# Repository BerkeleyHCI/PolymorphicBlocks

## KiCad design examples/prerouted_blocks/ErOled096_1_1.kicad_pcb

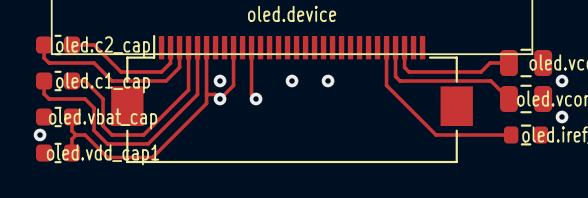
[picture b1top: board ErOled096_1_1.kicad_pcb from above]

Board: 4 copper layers, 9 parts (0 on the bottom side), 10 nets.

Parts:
oled.c1_cap, oled.c2_cap, oled.vbat_cap, oled.vdd_cap1: C_0603_1608Metric
oled.device: AFC01-S30FCA-00; Hirose_FH12-30S-0.5SH_1x30-1MP_P0.50mm_Horizontal
oled.iref_res: R_0603_1608Metric
oled.lcd: ER-OLED-0.96-1.1; Lcd_Er_Oled0.96_1.1_Outline
oled.vcc_cap, oled.vcomh_cap: C_0805_2012Metric

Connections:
gnd: oled.device.1, oled.device.8, oled.device.10, oled.device.12, oled.device.13, oled.device.15, oled.device.16, oled.device.17, oled.device.21, oled.device.22, oled.device.23, oled.device.24, oled.device.25, oled.device.29, oled.device.30, oled.iref_res.2, oled.vbat_cap.2, oled.vcc_cap.2, oled.vcomh_cap.2, oled.vdd_cap1.2
i2c_pull.i2c.sda: oled.device.19, oled.device.20
oled.c1_cap.neg: oled.c1_cap.2, oled.device.5
oled.c1_cap.pos: oled.c1_cap.1, oled.device.4
oled.c2_cap.neg: oled.c2_cap.2, oled.device.3
oled.c2_cap.pos: oled.c2_cap.1, oled.device.2
oled.device.vcc: oled.device.28, oled.vcc_cap.1
oled.device.vcomh: oled.device.27, oled.vcomh_cap.1
oled.iref_res.a: oled.device.26, oled.iref_res.1
v3v3: oled.device.6, oled.device.9, oled.device.11, oled.vbat_cap.1, oled.vdd_cap1.1

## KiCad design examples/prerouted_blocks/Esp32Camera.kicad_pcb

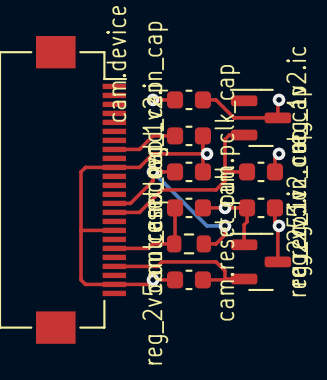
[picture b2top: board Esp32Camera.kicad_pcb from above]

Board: 2 copper layers, 11 parts (0 on the bottom side), 7 nets.

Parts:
cam.device: AFC01-S24FCA-00 (Jushuo); Hirose_FH12-24S-0.5SH_1x24-1MP_P0.50mm_Horizontal
cam.dovdd_cap, cam.pclk_cap, cam.reset_cap: C_0603_1608Metric
cam.reset_pull: R_0603_1608Metric
reg_1v2.ic: XC6206P122MR-G (Torex Semiconductor Ltd); SOT-23
reg_1v2.in_cap, reg_1v2.out_cap, reg_2v5.in_cap, reg_2v5.out_cap: C_0603_1608Metric
reg_2v5.ic: XC6206P252MR (Torex Semiconductor Ltd); SOT-23

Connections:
cam.device.reset: cam.device.19, cam.reset_cap.1, cam.reset_pull.2
cam.dvp8.pclk: cam.device.8, cam.pclk_cap.1
gnd: cam.device.10, cam.device.17, cam.device.23, cam.dovdd_cap.2, cam.pclk_cap.2, cam.reset_cap.2, reg_1v2.ic.1, reg_1v2.in_cap.2, reg_1v2.out_cap.2, reg_2v5.ic.1, reg_2v5.in_cap.2, reg_2v5.out_cap.2
pwr: reg_1v2.ic.3, reg_1v2.in_cap.1, reg_2v5.ic.3, reg_2v5.in_cap.1
v1v2: cam.device.15, reg_1v2.ic.2, reg_1v2.out_cap.1
v2v5: cam.device.21, reg_2v5.ic.2, reg_2v5.out_cap.1
v3v3: cam.device.14, cam.dovdd_cap.1, cam.reset_pull.1

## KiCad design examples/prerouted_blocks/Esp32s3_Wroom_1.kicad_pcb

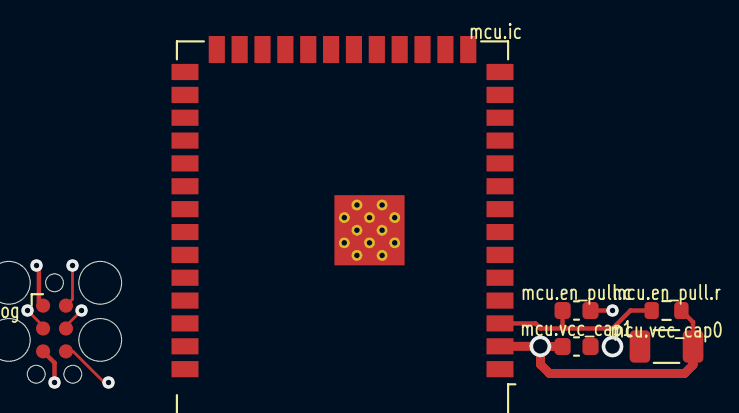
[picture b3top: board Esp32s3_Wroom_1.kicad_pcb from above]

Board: 4 copper layers, 6 parts (0 on the bottom side), 6 nets.

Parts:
mcu.en_pull.c, mcu.vcc_cap1: C_0603_1608Metric
mcu.en_pull.r: R_0603_1608Metric
mcu.ic: ESP32-S3-WROOM-1-N16R8; ESP32-S3-WROOM-1
mcu.prog: Tag-Connect_TC2030-IDC-FP_2x03_P1.27mm_Vertical
mcu.vcc_cap0: C_1206_3216Metric

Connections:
gnd: mcu.en_pull.c.2, mcu.ic.1, mcu.ic.40, mcu.ic.41, mcu.prog.5, mcu.vcc_cap0.2, mcu.vcc_cap1.2
mcu.program_boot_node: mcu.ic.27, mcu.prog.2
mcu.program_en_node: mcu.en_pull.c.1, mcu.en_pull.r.2, mcu.ic.3, mcu.prog.6
mcu.program_uart_node.a_tx: mcu.ic.37, mcu.prog.3
mcu.program_uart_node.b_tx: mcu.ic.36, mcu.prog.4
v3v3: mcu.en_pull.r.1, mcu.ic.2, mcu.prog.1, mcu.vcc_cap0.1, mcu.vcc_cap1.1

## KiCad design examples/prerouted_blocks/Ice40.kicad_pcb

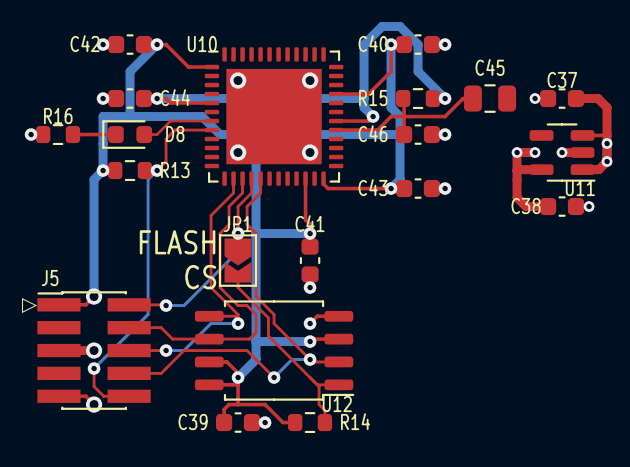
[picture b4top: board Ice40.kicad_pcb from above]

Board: 2 copper layers, 20 parts (0 on the bottom side), 12 nets.

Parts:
C37, C38, C39, C40, C41, C42, C43, C44, C46: C_0603_1608Metric
C45: C_0805_2012Metric
D8: KT-0603R (Hubei KENTO Elec) - Red 615~630nm 1.9~2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; LED_0603_1608Metric
J5: PinHeader1.27 Shrouded 2x5 (Generic); PinHeader_2x05_P1.27mm_Vertical_SMD
JP1: SolderJumper-2_P1.3mm_Open_TrianglePad1.0x1.5mm
R13, R14, R15, R16: R_0603_1608Metric
U10: ICE40UP5K-SG48 (Lattice Semiconductor Corporation); QFN-48-1EP_7x7mm_P0.5mm_EP5.3x5.3mm
U11: LP5907MFX-1.2/NOPB (Texas Instruments); SOT-23-5
U12: W25Q128JVSIQ (Winbond Electronics); SOIC-8_5.23x5.23mm_P1.27mm

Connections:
cdone.res.a: D8.1, R16.1
fpga.cdone: D8.2, U10.7
fpga.cs_jmp.output: JP1.2, R14.2, U12.1
fpga.ic.creset_b: J5.10, R13.2, U10.8
fpga.ic.spi_config.miso: J5.8, U10.17, U12.2
fpga.ic.spi_config.mosi: J5.6, U10.14, U12.5
fpga.ic.spi_config.sck: J5.4, U10.15, U12.6
fpga.ic.spi_config_cs: J5.2, JP1.1, U10.16
fpga.pll_res.pwr_out: C45.1, C46.1, R15.2, U10.29
fpga.vcc_reg.pwr_out: C38.1, C44.1, R15.1, U10.5, U10.30, U11.5
gnd: C37.2, C38.2, C39.2, C40.2, C41.2, C42.2, C43.2, C44.2, C45.2, C46.2, J5.3, J5.5, J5.9, R16.2, U10.49, U11.2, U12.4
v3v3: C37.1, C39.1, C40.1, C41.1, C42.1, C43.1, J5.1, R13.1, R14.1, U10.1, U10.22, U10.24, U10.33, U11.1, U11.3, U12.3, U12.7, U12.8

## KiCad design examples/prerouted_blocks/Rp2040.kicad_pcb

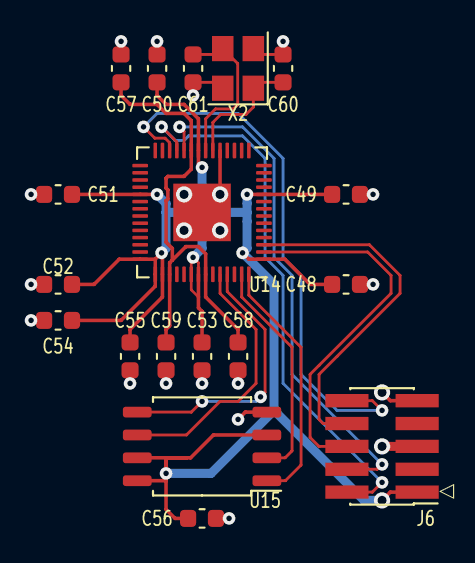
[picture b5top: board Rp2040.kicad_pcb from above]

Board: 2 copper layers, 18 parts (0 on the bottom side), 14 nets.

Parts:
C48, C49, C50, C51, C52, C53, C54, C55, C56, C57, C58, C59, C60, C61: C_0603_1608Metric
J6: PinHeader1.27 Shrouded 2x5 (Generic); PinHeader_2x05_P1.27mm_Vertical_SMD
U14: RP2040 (Raspberry Pi); QFN-56-1EP_7x7mm_P0.4mm_EP3.2x3.2mm
U15: W25Q128JVSIQ (Winbond Electronics); SOIC-8_5.23x5.23mm_P1.27mm
X2: Crystal_SMD_3225-4Pin_3.2x2.5mm

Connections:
gnd: C48.2, C49.2, C50.2, C51.2, C52.2, C53.2, C54.2, C55.2, C56.2, C57.2, C58.2, C59.2, C60.2, C61.2, J6.3, J6.5, J6.9, U14.19, U14.57, U15.4, X2.2, X2.4
mcu.crystal.crystal.a: C60.1, U14.20, X2.1
mcu.crystal.crystal.b: C61.1, U14.21, X2.3
mcu.ic.qspi.miso: U14.55, U15.2
mcu.ic.qspi.mosi: U14.53, U15.5
mcu.ic.qspi.sck: U14.52, U15.6
mcu.ic.qspi_cs: U14.56, U15.1
mcu.ic.vreg_vout: C57.1, C58.1, C59.1, U14.23, U14.45, U14.50
mcu.swd.swd.reset: J6.10, U14.26
mcu.swd.swd.swclk: J6.4, U14.24
mcu.swd.swd.swdio: J6.2, U14.25
mcu.swd.swo: J6.6, U14.2
mcu.swd.tdi: J6.8, U14.3
v3v3: C48.1, C49.1, C50.1, C51.1, C52.1, C53.1, C54.1, C55.1, C56.1, J6.1, U14.1, U14.10, U14.22, U14.33, U14.42, U14.43, U14.44, U14.48, U14.49, U15.3, U15.7, U15.8

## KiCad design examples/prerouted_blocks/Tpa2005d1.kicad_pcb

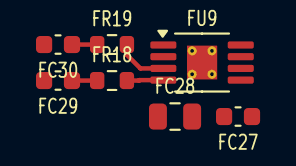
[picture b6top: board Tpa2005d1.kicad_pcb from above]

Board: 2 copper layers, 7 parts (0 on the bottom side), 6 nets.

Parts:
FC27: spk_drv.pwr_cap; C_0603_1608Metric
FC28: spk_drv.bulk_cap; C_0805_2012Metric
FC29: spk_drv.inp_cap; C_0603_1608Metric
FC30: spk_drv.inn_cap; C_0603_1608Metric
FR18: spk_drv.inp_res; R_0603_1608Metric
FR19: spk_drv.inn_res; R_0603_1608Metric
FU9: spk_drv.ic; MSOP-8-1EP_3x3mm_P0.65mm_EP1.68x1.88mm_ThermalVias

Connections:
Fgnd: FC27.2, FC28.2, FC30.2, FU9.7, FU9.9
Fspk_drv.ic.inn: FR19.2, FU9.3
Fspk_drv.ic.inp: FR18.2, FU9.4
Fspk_drv.inn_res.input: FC30.1, FR19.1
Fspk_drv.inp_res.input: FC29.1, FR18.1
Fv5: FC27.1, FC28.1, FU9.1, FU9.6

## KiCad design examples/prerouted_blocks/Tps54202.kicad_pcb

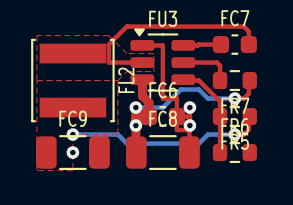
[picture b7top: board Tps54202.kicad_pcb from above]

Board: 2 copper layers, 9 parts (0 on the bottom side), 7 nets.

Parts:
FC6: reg_3v3.hf_in_cap; C_0603_1608Metric
FC7: reg_3v3.boot_cap; C_0603_1608Metric
FC8: reg_3v3.power_path.in_cap; C_1206_3216Metric
FC9: reg_3v3.power_path.out_cap; C_1206_3216Metric
FL2: reg_3v3.power_path.inductor; L_Sunlord_SWPA4030S
FR5: reg_3v3.fb.top_res; R_0603_1608Metric
FR6: reg_3v3.fb.bottom_res; R_0603_1608Metric
FR7: reg_3v3.en_res; R_0603_1608Metric
FU3: reg_3v3.ic; SOT-23-6

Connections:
Fgnd: FC6.2, FC8.2, FC9.2, FR6.2, FU3.1
Freg_3v3.ic.boot: FC7.1, FU3.6
Freg_3v3.ic.en: FR7.2, FU3.5
Freg_3v3.ic.fb: FR5.2, FR6.1, FU3.4
Freg_3v3.ic.sw: FC7.2, FL2.1, FU3.2
Fv3v3: FC9.1, FL2.2, FR5.1
Fvin: FC6.1, FC8.1, FR7.1, FU3.3

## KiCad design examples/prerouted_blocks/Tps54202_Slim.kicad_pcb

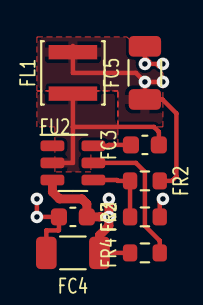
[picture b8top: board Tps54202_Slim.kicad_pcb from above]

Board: 2 copper layers, 9 parts (0 on the bottom side), 7 nets.

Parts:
FC2: reg_5v.hf_in_cap; C_0603_1608Metric
FC3: reg_5v.boot_cap; C_0603_1608Metric
FC4: reg_5v.power_path.in_cap; C_1206_3216Metric
FC5: reg_5v.power_path.out_cap; C_1206_3216Metric
FL1: reg_5v.power_path.inductor; L_Sunlord_SWPA3015S
FR2: reg_5v.fb.top_res; R_0603_1608Metric
FR3: reg_5v.fb.bottom_res; R_0603_1608Metric
FR4: reg_5v.en_res; R_0603_1608Metric
FU2: reg_5v.ic; SOT-23-6

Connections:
Fgnd: FC2.2, FC4.2, FC5.2, FR3.2, FU2.1
Freg_5v.ic.boot: FC3.1, FU2.6
Freg_5v.ic.en: FR4.2, FU2.5
Freg_5v.ic.fb: FR2.2, FR3.1, FU2.4
Freg_5v.ic.sw: FC3.2, FL1.1, FU2.2
Fv5: FC5.1, FL1.2, FR2.1
Fvin: FC2.1, FC4.1, FR4.1, FU2.3
